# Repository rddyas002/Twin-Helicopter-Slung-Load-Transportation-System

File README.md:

# Twin-Helicopter Slung Load Transportation System
This repository contains all the hardware and software development that was done for the Twin-Helicopter Slung Load Transportaton System project.

## Folder Hierarchy
-> root <br/>
---> Hardware	(Contain schematics and PCB designs)<br/>
-----> Aerial Application Board 2<br/>
-----> RadioInterface-v2<br/>
--->Software	(Contain source code)<br/>
-----> Aerial Application Board	(firmware for main avionics board)<br/>
-----> Base Station<br/>
--------> Archived	(old development code)<br/>
--------> MotionCatureSlave	(Image processing code that runs on uMocap slave PCs)<br/>
--------> MotionCaptureSlaveOnServer	<br/>
--------> UAVControl	(Main base-station software, command and control, state-estimation)<br/>
-----> Radio Multiplexer	(firmware for radio multiplexer board)<br/>

## Simulations and Videos
1. Single helicopter position control test <https://youtu.be/7Kq4-oiGThU>
2. Simulation showing trajectory tracking of translation and attitude <https://youtu.be/bJs7ehfYPP0>

Repository maintained by Yashren Reddi <br/>
E-mail: yashren.reddi@uct.ac.za

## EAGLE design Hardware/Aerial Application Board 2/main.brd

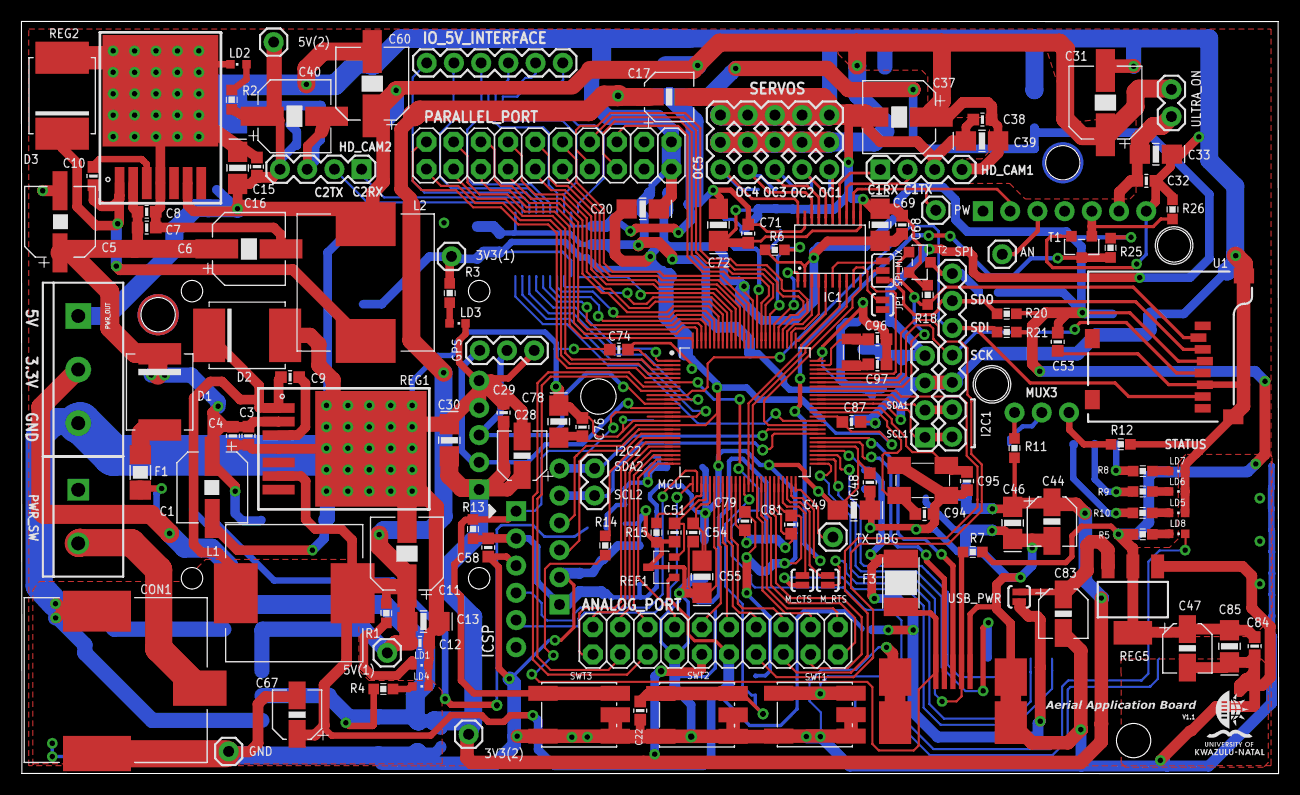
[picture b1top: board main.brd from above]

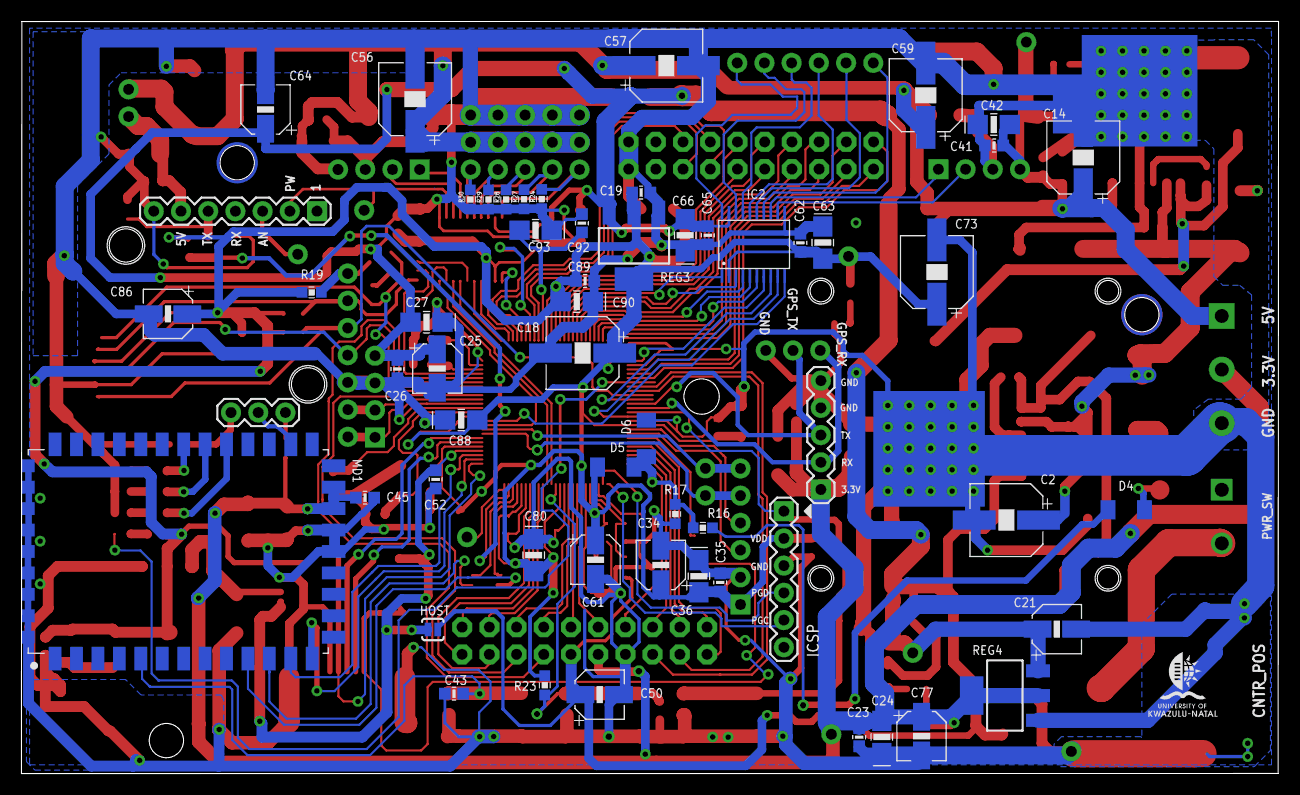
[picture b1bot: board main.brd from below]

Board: 2 copper layers, 117.3 x 70.2 mm, 193 parts (56 on the bottom side), 142 nets.

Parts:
3V3(1), 3V3(2), 5V(1), 5V(2): M01PTH; 1X01
AN: M01PTH; 1X01
ANALOG_PORT: M10X2; 2X10
C1, C5: 15uF50V; NAZT150M50V6.3X6.3NBF
C2, C6: 15uF50V; 6.3X5.5
C3, C4, C7, C8: 220nF25V; 0603
C9, C10: 10nF50V; 0603
C11, C14, C18, C31, C37, C40, C56, C57, C59, C60, C73: 100uF16V; 6.3X5.5
C12, C15, C19, C22, C23, C26, C29, C32, C35, C38, C41, C43, C45, C48, C51, C52, C53, C54, C58, C62, C65, C68, C71, C74, C76, C79, C81, C84, C87, C89, C92: 100nF16V; 0603
C13, C16, C27, C33, C39, C42, C66, C72: 10uF16V; EIA3216-18
C17, C21, C25, C50, C64, C67, C83: 22uF10V; 4X6.3
C20, C24, C30, C36, C46, C49, C55, C63, C69, C78, C80, C85, C88, C90, C93: 10uF6.3V; EIA3216-18
C28, C34, C44, C47, C61, C77, C86: 22uF6.3V; 4X6.3
C94, C95: 18pF; 0603
C96, C97: 8.2pF; 0603
CON1: POWERJACK
D1: SSC54-E3/57T; DO-214AB(SMC)
D2, D3: B360; SMC
D4, D5, D6: FDLL4148X; MELF-MLL34
F1: FUSE_MAIN; 3413.0223.22
F3: FUSE; MF-MSMF020-2
GND: M01PTH; 1X01
GPS: 1X03
HD1: 9DOF_SENSORSTICK; SENSOR_STICK
HD2: LS20031
HD3: EZ3
HD4: BMP085; BAROMETER
HD_CAM1, HD_CAM2: 1X04
HOST: SJ_2S-NO
I2C1, I2C2: 1X02
IC1, IC2: MAX3002-2; U20-3
IO_5V_INTERFACE: 1X06
JP1: SJ_2S-NO
L1, L2: B82477G; 12X12MM_PACK
LD1: 5V_1; CHIPLED_0603
LD2: 5V_2; CHIPLED_0603
LD3: 3V3_1; CHIPLED_0603
LD4: 3V3_2; CHIPLED_0603
LD5: ASSOC.; CHIPLED_0603
LD6: DATA TX; CHIPLED_0603
LD7: CONNECT; CHIPLED_0603
LD8: BOOT; CHIPLED_0603
MCU: PIC32MX795F512L; TQFP100_12MM
MD1: WIFLY2; WIFIFLY2
MUX3: 1X03
M_CTS: SJ_2S-NO
M_RTS: SJ_2S-NO
PARALLEL_PORT: M10X2; 2X10
PW: M01PTH; 1X01
PWR_OUT: SCREWTERMINAL-5MM-3
PWR_SW: SCREWTERMINAL-5MM-2
R1, R2: 470R; 0603
R3, R4, R5, R8, R9, R10: 220R; 0603
R6, R7, R11, R12, R13, R14, R18, R19, R20, R21, R23, R24, R25, R26, R27, R28, R29, R30: 10k; 0603
R15: RES0603; 0603
R16: 1M; 0603
R17: 180k; 0603
REF1: REF3133AIDBZTG4; SOT-23-3
REG1, REG2: LM2676; TO-263
REG3, REG4, REG5: LM1117IDT3.3; SOT223
SERVOS: RX_SERVO_STACK; SERVO_HEADER
SPI: 1X05
SPI_MUX: SJ_3
SWT1: RESET_WIFI; TACT
SWT2: PROGRAM; TACT
SWT3: RESET_MCU; TACT
T1, T2: 2N7002; MOSFET
TX_DBG: M01PTH; 1X01
U1: MICROSD; MICRO-SD-SOCKET-PP
U$46: ICSP
U$47: USBMINIB2
ULTRA_ON: 1X02
USB_PWR: SJ_2S-NO
X2: 32.786kHz; 1.5X3.2MM_SMD_RTCC
X3: 8MHz; 3.2X5MM_SMD_CRYSTAL

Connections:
3.3V_(1): 3V3(1).1, C18.+, C19.1, C20.C, C34.C, C35.1, C36.C, C47.C, C48.1, C49.C, C53.1, C54.1, C55.C, C58.1, C61.C, C62.1, C63.C, C68.1, C69.C, C73.+, C74.1, C76.1, C78.C, C79.1, C80.C, C81.1, C84.1, C85.C, C86.C, C87.1, C88.C, C89.1, C90.C, D5.1, HD4.1, IC1.2, IC2.2, MCU.2, MCU.16, MCU.30, MCU.37, MCU.46, MCU.55, MCU.62, MCU.86, R3.2, R5.2, R6.2, R7.2, R13.2, R19.1, R20.1, R21.1, R23.2, R25.1, REG3.2, REG3.4, REG5.2, REG5.4, U1.4, U$46.2
3.3V_(2): 3V3(2).1, ANALOG_PORT.9, C23.1, C24.C, C28.C, C29.1, C30.C, C44.C, C45.1, C46.C, C77.C, HD2.1, MD1.20, MD1.21, PWR_OUT.2, R4.2, R11.2, REG4.2, REG4.4
5V_(1): 5V(1).1, ANALOG_PORT.11, C11.+, C12.1, C13.C, C17.C, C21.C, C25.C, C26.1, C27.C, C50.C, C64.C, C65.1, C66.C, C67.C, C71.1, C72.C, HD1.4, HOST.1, IC1.19, IC2.19, L1.2, R1.2, REF1.1, REG1.6, REG3.3, REG4.3
5V_(2): 5V(2).1, C14.+, C15.1, C16.C, C31.+, C37.+, C38.1, C39.C, C40.+, C41.1, C42.C, C56.+, C57.+, C59.+, C60.+, HD_CAM1.4, HD_CAM2.4, L2.2, PWR_OUT.1, R2.2, REG2.6, SERVOS.2, SERVOS.5, SERVOS.8, SERVOS.11, SERVOS.14, ULTRA_ON.2
12V_SAFE: C1.+, C2.+, C3.1, C4.1, C5.+, C6.+, C7.1, C8.1, D1.A, REG1.2, REG2.2
!CS: R19.2, SPI.1, T2.3
!MCLR: MCU.13, R13.1, SWT3.3, SWT3.4, U$46.1
!SS1: MCU.69, R18.1, T2.1, U1.2
AERXD1/INT2/RE9: MCU.19, R14.2
AERXERR/RG1_5V: IC2.14, IO_5V_INTERFACE.6
AERXERR/RG15: IC2.7, MCU.1
AN0: D5.2, D6.1, MCU.25, R16.1, R17.1
AN1: ANALOG_PORT.8, MCU.24
AN2: ANALOG_PORT.6, MCU.23
AN3: ANALOG_PORT.4, MCU.22
AN4: ANALOG_PORT.2, MCU.21
AN5: ANALOG_PORT.1, MCU.20
AN8: ANALOG_PORT.10, MCU.32
AN9: ANALOG_PORT.12, MCU.33
AN10: ANALOG_PORT.14, MCU.34
AN11: ANALOG_PORT.16, MCU.35
AN12: ANALOG_PORT.18, MCU.41
AN13: ANALOG_PORT.20, MCU.42
AN14: ANALOG_PORT.19, MCU.43
AN15: ANALOG_PORT.17, MCU.44
AN_OUT5V: AN.1, HD3.3
C1RX/ETXD1/PMD11/RF0: MCU.87, PARALLEL_PORT.12
C1TX/ETXD0/PMD10/RF1: MCU.88, PARALLEL_PORT.11
C2RX/PMD8/RG0: MCU.90, PARALLEL_PORT.9
C2TX/ETXERR/PMD9/RG1: MCU.89, PARALLEL_PORT.10
CAM1_RX_IN: HD_CAM1.1, IC1.14
CAM1_TX_OUT: HD_CAM1.2, IC1.13
CAM2_RX_IN: HD_CAM2.1, IC2.13
CAM2_TX_OUT: HD_CAM2.2, IC2.12
CX9: C9.2, D2.A, L1.1, REG1.1
CX10: C10.2, D3.A, L2.1, REG2.1
D+: MCU.57, U$47.D+
D-: MCU.56, U$47.D-
DBG_TO_PC: MCU.50, TX_DBG.1
EMDC/AEMDC/IC4/PMCS1/PMA14/RD: ANALOG_PORT.13, MCU.71
EN1/RA4: IC1.10, MCU.60
EN2/RA5: IC2.10, MCU.61
EOC/INT1: HD4.3, MCU.18
ETXCLK/PMD15/CN16/RD7: MCU.84, PARALLEL_PORT.16
ETXD2/IC5/PMD12/RD12: MCU.79, PARALLEL_PORT.13
ETXD3/PMD13/CN19/RD13: MCU.80, PARALLEL_PORT.14
ETXEN/PMD14/CN15/RD6: MCU.83, PARALLEL_PORT.15
GND: ANALOG_PORT.7, C1.-, C2.-, C3.2, C4.2, C5.-, C6.-, C7.2, C8.2, C11.-, C12.2, C13.A, C14.-, C15.2, C16.A, C17.A, C18.-, C19.2, C20.A, C21.A, C22.2, C23.2, C24.A, C25.A, C26.2, C27.A, C28.A, C29.2, C30.A, C31.-, C32.2, C33.A, C34.A, C35.2, C36.A, C37.-, C38.2, C39.A, C40.-, C41.2, C42.A, C43.2, C44.A, C45.2, C46.A, C47.A, C48.2, C49.A, C50.A, C51.2, C52.2, C53.2, C54.2, C55.A, C56.-, C57.-, C58.2, C59.-, C60.-, C61.A, C62.2, C63.A, C64.A, C65.2, C66.A, C67.A, C68.2, C69.A, C71.2, C72.A, C73.-, C74.2, C76.2, C77.A, C78.A, C79.2, C80.A, C81.2, C83.A, C84.2, C85.A, C86.A, C87.2, C88.A, C89.2, C90.A, C92.2, C93.A, C94.2, C95.1, C96.2, C97.2, CON1.P$2, CON1.P$3, D2.C, D3.C, D6.2, GND.1, GPS.3, HD1.3, HD2.4, HD2.5, HD3.7, HD4.2, HD_CAM1.3, HD_CAM2.3, IC1.11, IC2.11, LD1.C, LD2.C, LD3.C, LD4.C, LD5.C, LD6.C, LD7.C, MCU.15, MCU.31, MCU.36, MCU.45, MCU.65, MCU.75, MD1.18, MD1.19, MD1.36, MD1.37, MD1.38, MD1.39, MD1.40, MD1.41, MD1.42, MD1.43, MD1.44, PARALLEL_PORT.19, PARALLEL_PORT.20, PWR_OUT.3, R12.1, R15.2, R17.2, R18.2, R24.1, R26.2, R27.1, R28.1, R29.1, R30.1, REF1.3, REG1.4, REG1.8, REG1.9, REG2.4, REG2.8, REG2.9, REG3.1, REG4.1, REG5.1, SERVOS.3, SERVOS.6, SERVOS.9, SERVOS.12, SERVOS.15, SPI.5, SWT1.1, SWT1.2, SWT1.5, SWT2.1, SWT2.2, SWT2.5, SWT3.1, SWT3.2, SWT3.5, T1.2, T2.2, U1.6, U1.GND1, U1.GND3, U$46.3, U$47.GND, U$47.GND@1, U$47.GND@2, U$47.GND@3, U$47.GND@4, X3.2, X3.4
L2: C10.1, REG2.3
MCU_!CTS: MCU.47, M_CTS.2
MCU_!RTS: MCU.48, M_RTS.1
MCU_U5RX: IC1.8, MCU.40
MCU_U5TX: IC1.7, MCU.39
MCU_U6RX: IC2.9, MCU.14
MCU_U6TX: IC2.8, MCU.10
unnamed: IC1.9, JP1.1
unnamed: LD1.A, R1.1
unnamed: LD2.A, R2.1
unnamed: C9.1, REG1.3
unnamed: LD3.A, R3.1
unnamed: LD4.A, R4.1
unnamed: CON1.P$1, PWR_SW.2
unnamed: C83.C, REG5.3, USB_PWR.2
unnamed: LD8.A, R5.1
unnamed: C43.1, MD1.5, SWT1.3, SWT1.4
unnamed: C32.1, C33.C, HD3.6, ULTRA_ON.1
unnamed: D1.C, F1.2
unnamed: MD1.24, MUX3.2
unnamed: MUX3.1, R11.1
unnamed: MD1.29, R8.1
unnamed: LD7.A, R8.2
unnamed: MD1.28, R9.1
unnamed: LD6.A, R9.2
unnamed: MD1.27, R10.1
unnamed: LD5.A, R10.2
unnamed: MUX3.3, R12.2
unnamed: D4.1, R16.2
OC1: IC1.6, SPI_MUX.1
OC1_5V: IC1.15, R30.2, SERVOS.13
OC2: IC1.5, MCU.76
OC2_5V: IC1.16, R29.2, SERVOS.10
OC3: IC1.4, MCU.77
OC3_5V: IC1.17, R28.2, SERVOS.7
OC4: IC1.3, MCU.78
OC4_5V: IC1.18, R27.2, SERVOS.4
OC5: IC1.1, MCU.81
OC5_5V: IC1.20, R24.2, SERVOS.1
OSC1: C94.1, MCU.63, X3.1
OSC2: C95.2, MCU.64, X3.3
PGEC2: MCU.26, U$46.5
PGED2: MCU.27, U$46.4
PMD0/RE0: MCU.93, PARALLEL_PORT.8
PMD1/RE1: MCU.94, PARALLEL_PORT.7
PMD2/RE2: MCU.98, PARALLEL_PORT.6
PMD3/RE3: MCU.99, PARALLEL_PORT.5
PMD4/RE4: MCU.100, PARALLEL_PORT.4
PMD5/RE5: MCU.3, PARALLEL_PORT.3
PMD6RE6: MCU.4, PARALLEL_PORT.1
PMD7/RE7: MCU.5, PARALLEL_PORT.2
PMRD/CN14/RD5: MCU.82, R6.1
PROGRAM/RA1: C22.1, MCU.38, R23.1, SWT2.3, SWT2.4
PW_OUT5V: HD3.2, IC1.12, PW.1
RA0/XCLR: HD4.4, MCU.17
RTCC/EMDIO/AEMDIO/IC1/RD8: ANALOG_PORT.15, JP1.2, MCU.68
RX_GPS_IN: GPS.1, HD2.2, MCU.12
SCK1: MCU.70, SPI.4, U1.5
SCL1: HD1.1, I2C1.1, MCU.66
SCL2: HD4.5, I2C2.2, MCU.58
SDA1: HD1.2, I2C1.2, MCU.67
SDA2: HD4.6, I2C2.1, MCU.59
SDI1: MCU.9, R21.2, SPI.3, U1.7
SDO1: R20.2, SPI.2, SPI_MUX.3, U1.3
SDO1/OC1: MCU.72, SPI_MUX.2
SOSCI: C97.1, MCU.73, X2.2
SOSCO: C96.1, MCU.74, X2.1
SWT_BATT: D4.2, F1.1, PWR_SW.1
T2CK/RC1: LD8.C, MCU.6
T3CK/AC2TX/RC2: ANALOG_PORT.5, MCU.7
T4CK/AC2RX/RC3: ANALOG_PORT.3, MCU.8
TRCLK/RA6: IC2.1, MCU.91
TRCLK/RA6_5V: IC2.20, IO_5V_INTERFACE.1
TRD0/RG13: IC2.6, MCU.97
TRD0/RG13_5V: IC2.15, IO_5V_INTERFACE.5
TRD1/RG12: IC2.5, MCU.96
TRD1/RG12_5V: IC2.16, IO_5V_INTERFACE.4
TRD2/RG14: IC2.4, MCU.95
TRD2/RG14_5V: IC2.17, IO_5V_INTERFACE.3
TRD3/RA7: IC2.3, MCU.92
TRD3/RA7_5V: IC2.18, IO_5V_INTERFACE.2
TX_GPS_OUT: GPS.2, HD2.3, MCU.11
ULTRA_TX3V: MCU.49, R25.2, T1.3
USBID: MCU.51, R7.1, U$47.ID
US_TX_OUT5V: HD3.5, R26.1, T1.1
VBUS: F3.1, R14.1, U$47.VBUS
VBUS_SAFE: C52.1, F3.2, HOST.2, MCU.54, USB_PWR.1
VCAP/VDDCORE: C92.1, C93.C, MCU.85
VREF+: C51.1, MCU.29, REF1.2
VREF-: MCU.28, R15.1
WIFLY_!CTS: MD1.11, M_RTS.2
WIFLY_!RTS: MD1.10, M_CTS.1
WIFLY_RX: MCU.53, MD1.12
WIFLY_TX: MCU.52, MD1.13

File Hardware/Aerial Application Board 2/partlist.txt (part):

Partlist

Exported from main.sch at 2011/10/19 10:26:58 AM

EAGLE Version 5.1.0 Copyright (c) 1988-2008 CadSoft

Part            Value            Device                Package               Library         Sheet

3V3(1)          M01PTH           M01PTH                1X01                  SparkFun        1
3V3(2)          M01PTH           M01PTH                1X01                  SparkFun        1
5V(1)           M01PTH           M01PTH                1X01                  SparkFun        1
5V(2)           M01PTH           M01PTH                1X01                  SparkFun        1
AN              M01PTH           M01PTH                1X01                  SparkFun        1
ANALOG_PORT     M10X2            M10X2                 2X10                  SparkFun        1
C1              15uF50V          NAZT150M50V6.3X6.3NBF NAZT150M50V6.3X6.3NBF cap             1
C2              15uF50V          CAP100UF16V           6.3X5.5               cap             1
C3              220nF25V         CAP_0603_CER          0603                  cap             1
C4              220nF25V         CAP_0603_CER          0603                  cap             1
C5              15uF50V          NAZT150M50V6.3X6.3NBF NAZT150M50V6.3X6.3NBF cap             1
C6              15uF50V          CAP100UF16V           6.3X5.5               cap             1
C7              220nF25V         CAP_0603_CER          0603                  cap             1
C8              220nF25V         CAP_0603_CER          0603                  cap             1
C9              10nF50V          CAP_0603_CER          0603                  cap             1
C10             10nF50V          CAP_0603_CER          0603                  cap             1
C11             100uF16V         CAP100UF16V           6.3X5.5               cap             1
C12             100nF16V         CAP_0603_CER          0603                  cap             1
C13             10uF16V          CAP_POL_TANT3216      EIA3216-18            cap             1
C14             100uF16V         CAP100UF16V           6.3X5.5               cap             1
C15             100nF16V         CAP_0603_CER          0603                  cap             1
C16             10uF16V          CAP_POL_TANT3216      EIA3216-18            cap             1
C17             22uF10V          CAP4X6.3MM            4X6.3                 cap             1
C18             100uF16V         CAP100UF16V           6.3X5.5               cap             1
C19             100nF16V         CAP_0603_CER          0603                  cap             1
C20             10uF6.3V         CAP_POL_TANT3216      EIA3216-18            cap             1
C21             22uF10V          CAP4X6.3MM            4X6.3                 cap             1
C22             100nF16V         CAP_0603_CER          0603                  cap             1
C23             100nF16V         CAP_0603_CER          0603                  cap             1
C24             10uF6.3V         CAP_POL_TANT3216      EIA3216-18            cap             1
C25             22uF10V          CAP4X6.3MM            4X6.3                 cap             1
C26             100nF16V         CAP_0603_CER          0603                  cap             1
C27             10uF16V          CAP_POL_TANT3216      EIA3216-18            cap             1
C28             22uF6.3V         CAP4X6.3MM            4X6.3                 cap             1
C29             100nF16V         CAP_0603_CER          0603                  cap             1
C30             10uF6.3V         CAP_POL_TANT3216      EIA3216-18            cap             1
C31             100uF16V         CAP100UF16V           6.3X5.5               cap             1
C32             100nF16V         CAP_0603_CER          0603                  cap             1
C33             10uF16V          CAP_POL_TANT3216      EIA3216-18            cap             1
C34             22uF6.3V         CAP4X6.3MM            4X6.3                 cap             1
C35             100nF16V         CAP_0603_CER          0603                  cap             1
C36             10uF6.3V         CAP_POL_TANT3216      EIA3216-18            cap             1
C37             100uF16V         CAP100UF16V           6.3X5.5               cap             1
C38             100nF16V         CAP_0603_CER          0603                  cap             1
C39             10uF16V          CAP_POL_TANT3216      EIA3216-18            cap             1
C40             100uF16V         CAP100UF16V           6.3X5.5               cap             1
C41             100nF16V         CAP_0603_CER          0603                  cap             1
C42             10uF16V          CAP_POL_TANT3216      EIA3216-18            cap             1
C43             100nF16V         CAP_0603_CER          0603                  cap             1
C44             22uF6.3V         CAP4X6.3MM            4X6.3                 cap             1
C45             100nF16V         CAP_0603_CER          0603                  cap             1
C46             10uF6.3V         CAP_POL_TANT3216      EIA3216-18            cap             1
C47             22uF6.3V         CAP4X6.3MM            4X6.3                 cap             1
C48             100nF16V         CAP_0603_CER          0603                  cap             1
C49             10uF6.3V         CAP_POL_TANT3216      EIA3216-18            cap             1
C50             22uF10V          CAP4X6.3MM            4X6.3                 cap             1
C51             100nF16V         CAP_0603_CER          0603                  cap             1
C52             100nF16V         CAP_0603_CER          0603                  cap             1
C53             100nF16V         CAP_0603_CER          0603                  cap             1
C54             100nF16V         CAP_0603_CER          0603                  cap             1
C55             10uF6.3V         CAP_POL_TANT3216      EIA3216-18            cap             1
C56             100uF16V         CAP100UF16V           6.3X5.5               cap             1
C57             100uF16V         CAP100UF16V           6.3X5.5               cap             1
C58             100nF16V         CAP_0603_CER          0603                  cap             1
C59             100uF16V         CAP100UF16V           6.3X5.5               cap             1
C60             100uF16V         CAP100UF16V           6.3X5.5               cap             1
C61             22uF6.3V         CAP4X6.3MM            4X6.3                 cap             1
C62             100nF16V         CAP_0603_CER          0603                  cap             1
C63             10uF6.3V         CAP_POL_TANT3216      EIA3216-18            cap             1
C64             22uF10V          CAP4X6.3MM            4X6.3                 cap             1
C65             100nF16V         CAP_0603_CER          0603                  cap             1
C66             10uF16V          CAP_POL_TANT3216      EIA3216-18            cap             1
C67             22uF10V          CAP4X6.3MM            4X6.3                 cap             1
C68             100nF16V         CAP_0603_CER          0603                  cap             1
C69             10uF6.3V         CAP_POL_TANT3216      EIA3216-18            cap             1
C71             100nF16V         CAP_0603_CER          0603                  cap             1
C72             10uF16V          CAP_POL_TANT3216      EIA3216-18            cap             1
C73             100uF16V         CAP100UF16V           6.3X5.5               cap             1
C74             100nF16V         CAP_0603_CER          0603                  cap             1
C76             100nF16V         CAP_0603_CER          0603                  cap             1
C77             22uF6.3V         CAP4X6.3MM            4X6.3                 cap             1
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
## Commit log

2017-02-22 Upload readme
2017-02-22 Upload project
2017-08-08 Set theme jekyll-theme-cayman
